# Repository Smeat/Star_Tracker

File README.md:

# Goals of this fork
 * Add support for esp32
 * Use an sdmmc driver and be able to use a larger library
   * SIMBAD library for Vmag <11 is about 16mb for the data and 30mb for the names
 * Use a nokia 5110 LCD with red backlight LEDs
 * Visual representation on the screen
 * WiFi connection to KStars/Stellarium -> done with LX200
 * ESP32 support only for now (8bit support may return once the esp32 is running)
# Arduino Star Tracker

This project aims an **automatic control for telescopes**, is **based on Arduino** and is **low-cost**!

The control utilizes a calibration method and various settings which enable you to control **any type of mount** (not just equatorial and altazimuthal) pointed at any direction.

The **total cost** of upgrading your mount should be around **75 USD** (*SkyWatcher SynScan GOTO Upgrade for EQ3-2* costs around *460 USD*).

## Features

See [future work](#future-work) for missing features (like communication via USB or Bluetooth). Some implemented and working freatures:

* **Manual control** with various precision (degrees, arc minutes and arc seconds).
* **Automatic pointing** at predefined coordinates.
* Onboard **catalogue of deep sky objects** (the one which is present in Stellarium), so you can search thousands of Messier, Caldwell and NGC objects.
* Precise **tracking** (for any type of mount).
* **Parking** to default position.
* **Calibration** of **mount pole** which works similarly to All-Star polar alignement.
* **Camera control** which alows you to take photos with predefined exposure time and with a predefined period.
* **Wireless control** via IR remote control.
* Real **asynchronous** control of **stepper motors** (any other code can be run in parallel). 
* **LX200** support

## Hardware setup

#### 0. What you will need:
* **Arduino MEGA2560**, unfortunately Arduino Uno cannot be used due to the lack of memory
* **Power supply** or battery, e.g. *12V* and around *2.5A* (depends on your stepper motors)
* *2×* **NEMA 17** stepper motor (forget about 28BYJ!)
* *2×* stepper motor driver like **A4988**
* *2×* stepper driver **extender for A4988** (we will modify this part, so you should consider custom design with 100μF capacitor)
* *4×* **4k7** or **10k resistor** (or any other suitable resistor you hold in your hands)
* *(optionally)* **Gearboxes** for the motors (battery screwdriver is typically much cheaper than profi gearboxes and has some planetary gearboxes inside!)
* *2×* **flexible shaft couplers** for joing the motors with mount
* **Real Time Clock**, note that *DS3231* or more precise clocks are preffered over DS1307 
* **microSD Card module**
* **16×2 LCD** (without I2C module)
* **10k Potentiometer**
* **IR receiver**
* **Remote control**, you can use your favourite one you use for TV or you can use any other for makers! This repo settings match with a [remote control](https://www.makeblock.com/project/me-ir-remote-controller) by Makeblock. 
* Some kind of **transistor**, e. g. *BC337* and suitable resistor, e. g. *1k ohms* 
* **Bunch of wires and connectors**

#### 1. Parts modification and tuning

You should **add** the four **resistors** between `STEP`-`GND` and `DIR`-`GND` pins **to avoid a jitter** of stepper motors at startup. 

A typical extender for A4988 has an `ENABLE` pin, however, we do not need it. Instead, we **need a pin for controlling microstepping**. That is why you should hardwire the three microstepping pins and you should add a single pin to control them. Search for *microstepping resolution truth table* of A4988.

A **cheap IR remote control** might have a **weak diode**. In that case, you won't be able to control the mount from a distant places. So I recommend you to **replace the diode with a better one.**  

You also need to **tune potentiometers of stepper drivers**. Search for *How to set output current limit on A4988 stepper driver*. This can reduce noise produced by the motors or you can remove **problems with skipping of steps**. 

Use the **potentiometer** connected to the LCD to **adjust contrast**.

#### 2. Wiring

## Software Settings & Uploding to Arduino

#### 0. Prepearing libraries

The following list contains libraries you will need to sucessfuly compile the Star Tracker project (most of them is included in the Arduino IDE by default):

* [RTCLib](https://github.com/adafruit/RTClib)
* [LiquidCrystal](https://github.com/arduino-libraries/LiquidCrystal)
* [SD](https://github.com/arduino-libraries/SD)
* [SPI](https://www.arduino.cc/en/Reference/SPI)
* [Wire](https://www.arduino.cc/en/Reference/Wire)
* [EEPROM](https://www.arduino.cc/en/Reference/EEPROM)

At first, **make sure you have already installed all the libraries**.

#### 1. General configuration

Next, you should **modify** the `src/config.h` file to fit your needs. Familiarize yourself with all the definitions in the file. You should **definitely change** `LONGITUDE`, `LATITUDE`, `REDUCTION_RATIO_xx` and `DEG_PER_MOUNT_REV_xx` variables! You also need to change `DEFAULT_POLE_xx` if you use an altazimuthal mount.

You may encounter a problem with **stucked motors**. In that case, I advice you to **adjust** `ACCEL_STEPS_xx`, `ACCEL_DELAY_xx`, `FAST_DELAY_START_xx` and `FAST_DELAY_END_xx`. Change these definitions in order to change motors speed or ac/deceleration.

#### 2. Remote control

You need to **change definitions of key codes** to fit the protocol used by your favourite remote control. Take look **at the beginning** of the `src/keypad.h` file. There are few definitions of `KP_KEY_xx` where `xx` describes the particular key. To figure out **codes used by your remote control**, upload the following sketch to your Arduino:

```
#include <Arduino.h>
#include <IRremote.h>
#include "src/config.h"

IRrecv ir(KEYPAD_IR_PIN);
decode_results results;

void setup(){
    Serial.begin(9600);
    ir.enableIRIn();
}

void loop(){
    if (!ir.decode(&results)) {
      delay(5);
      return;
    }
    Serial.println(results.value, HEX);
    ir.resume();
    delay(500);
}
```

Then **open the Serial monitor** and **observe the key codes** of pressed keys. Note that you will receive `0xFFFFFFFF` when you hold a key continuously.

You can also **change mapping of these keys to particular actions** in the `src/control.h` file (but be careful as these keys and actions should not cause conflicts and ambiguity).

#### 3. SD card and catalogue

Take an **empty and formatted microSD** card and **copy there the content** of the `SD` directory. It should be a single file `catalog.csv` which is a limited version of **Stellarium catalogue of deep space objects**. You can delete or add object to this file, however the structure and meaning of columns should be preserved.

#### 4. Real Time Clock

The `src/rtc_ds3231.h` file contains implementation of `Clock` class for `DS3231` module. In case you use **other module** or you want to obtain time from NTP servers, **implement** the `Clock` interface and change some lines in `Star_Tracker.ino`.

#### 5. Camera trigger

Similarly, you may need to change the implementation of the camera trigger control. The `src/CanonEOS1000D.h` file contains implementation of `CameraController` class for *Canon EOS1000D*. If you have other camera with **other trigger logic**, you should **create a new implementation** of `CameraController` and change some lines at `Star_Tracker.ino`. Note that in this case, you may also need a different wiring!

## Notes on precision

The only loss of precision is caused by Arduino's floating point unit which cannot work with 64-bit floating point numbers. Especially while computing extremal values of some goniometric funcions (tangens and other functions which are reduced to computing tangens). These problems can occur while pointing to stars near celestial pole. The GoTo feature can miss few arc minutes and alignement can be imprecise in that case. However points with lower DEC values should be handled properly.  

The tracking with very badly aligned mount can also be imprecise after some time because the speeds of DEC and RA motors are computed just once at the start of the movement. Unfortunately these speeds does not have to be constant necessarily.

## Future work

- [ ] enable **serial communication** with *USB* and *Bluetooth*
- [ ]  better **speed** computation **while tracking**
- [ ]  compute **alignment analytically**

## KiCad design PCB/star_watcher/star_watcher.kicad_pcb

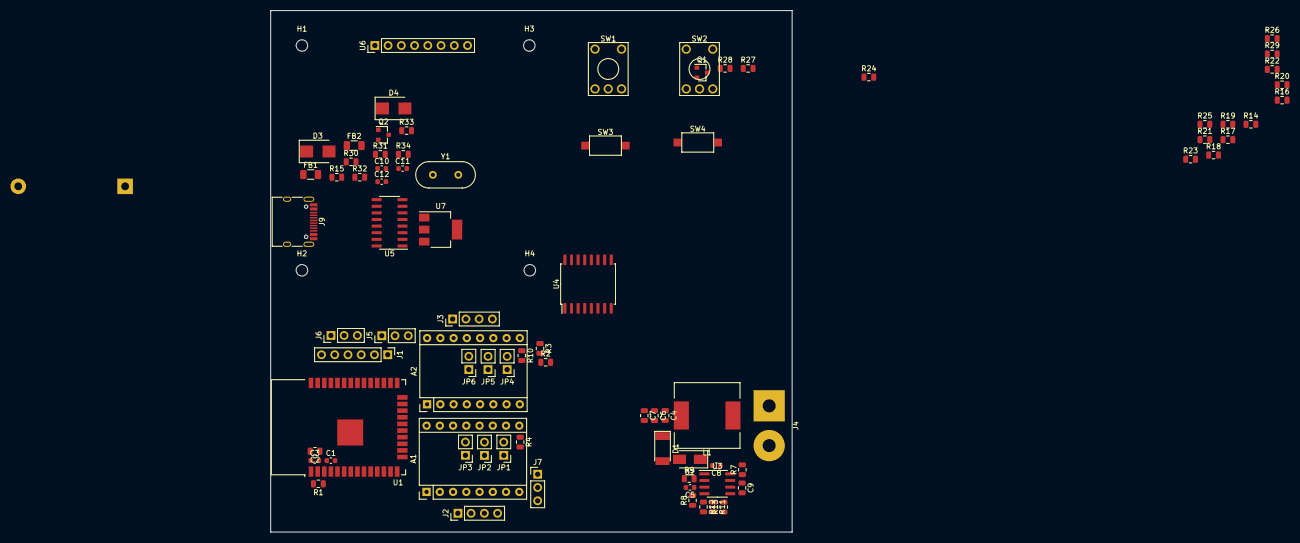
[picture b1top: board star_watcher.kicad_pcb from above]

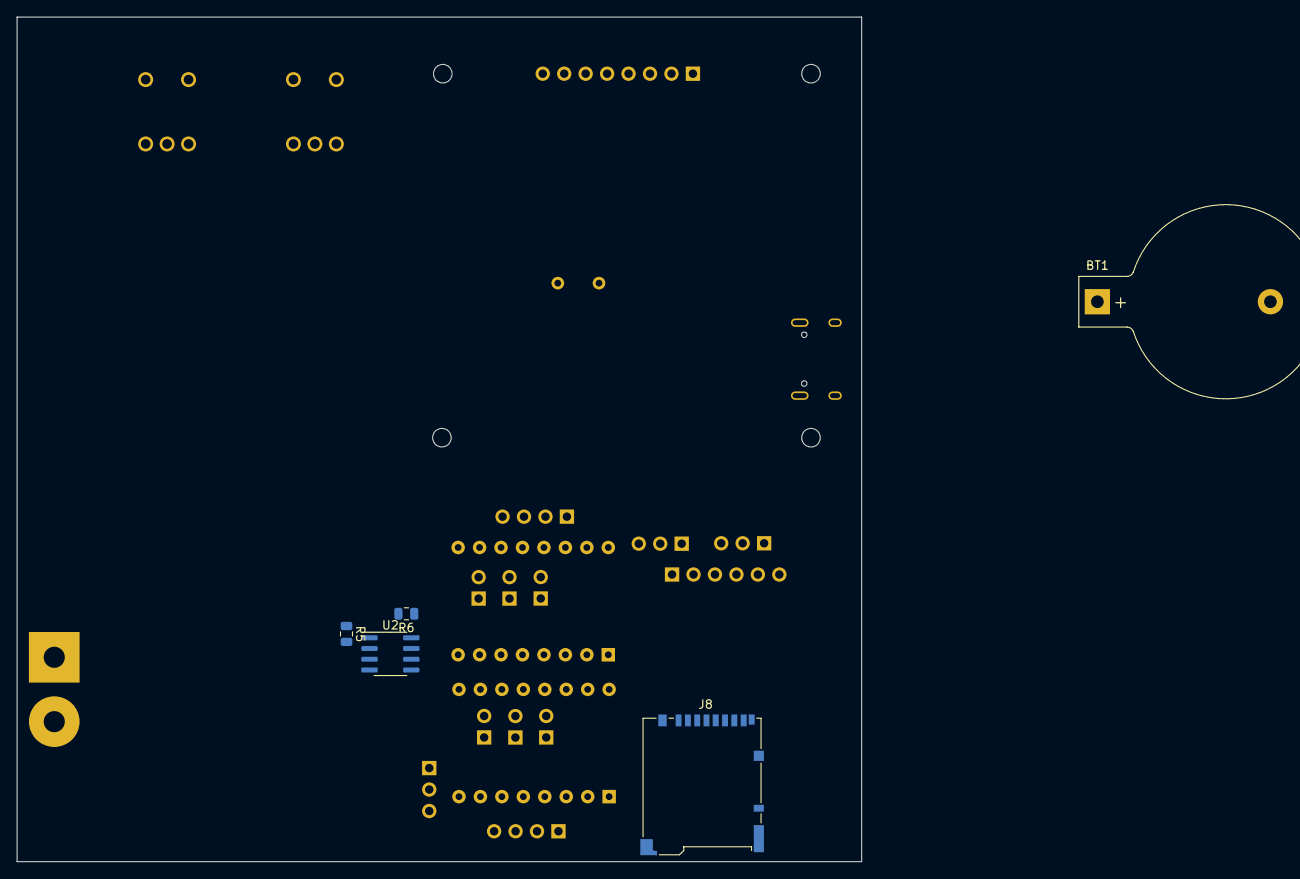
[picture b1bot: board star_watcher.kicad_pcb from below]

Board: 2 copper layers, 100.0 x 100.0 mm, 89 parts (5 on the bottom side), 78 nets, no tracks yet.

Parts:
A1, A2: Pololu_Breakout_A4988; Pololu_Breakout-16_15.2x20.3mm
BT1: Battery_Cell; BatteryHolder_Keystone_103_1x20mm
C1, C3, C8, C10: 0.1µF; C_0603_1608Metric
C2, C4, C6, C7, C9: 10µF; C_0805_2012Metric
C5: 150pF; C_0603_1608Metric
C11, C12: C; C_0603_1608Metric
D1: 3.5; D_MELF
D2: D_Schottky; D_SMA
D3, D4: D_TVS; D_SMB
FB1, FB2: Ferrite_Bead; L_1206_3216Metric
H1, H2, H3, H4: MountingHole; MountingHole_2.2mm_M2
J1: Programming; PinHeader_1x06_P2.54mm_Vertical
J2: Motor2; PinHeader_1x04_P2.54mm_Vertical
J3: Motor1; PinHeader_1x04_P2.54mm_Vertical
J4: input power; SolderWirePad_1x02_P7.62mm_Drill2.5mm
J5: UART1; PinHeader_1x03_P2.54mm_Vertical
J6: UART2; PinHeader_1x03_P2.54mm_Vertical
J7: I2C; PinHeader_1x03_P2.54mm_Vertical
J8: Micro_SD_Card_Det; microSD_HC_Hirose_DM3BT-DSF-PEJS
J9: USB_C_Receptacle_USB2.0; USB_C_Receptacle_HRO_TYPE-C-31-M-12
JP1, JP2, JP3, JP4, JP5, JP6: Jumper; PinHeader_1x02_P2.54mm_Vertical
L1: 22µH; L_12x12mm_H6mm
Q1, Q2: Q_PMOS_DGS; SOT-23
R1, R3, R4, R5, R6, R17, R18, R19, R20, R21, R22, R23, R24, R25, R26, R27, R28, R29: 10k; R_0805_2012Metric
R2: 240k; R_0805_2012Metric
R7, R8, R10: 100k; R_0805_2012Metric
R9: 59k; R_0805_2012Metric
R11, R14, R15, R16, R30, R31, R32, R33, R34: R; R_0805_2012Metric
R12: 40.2k; R_0805_2012Metric
R13: 200k; R_0805_2012Metric
SW1, SW2: Rotary_Encoder_Switch; KSA_Tactile_SPST
SW3, SW4: SW_Push; SW_SPST_CK_RS282G05A3
U1: ESP32-WROOM-32U; ESP32-WROOM-32
U2: DS3231MZ; SOIC-8_3.9x4.9mm_P1.27mm
U3: MP1584; SOIC-8_3.9x4.9mm_P1.27mm
U4: PCF8574; SOIC-16W_7.5x10.3mm_P1.27mm
U5: CH340G; SOIC-16_3.9x9.9mm_P1.27mm
U6: 5110; PinHeader_1x08_P2.54mm_Vertical
U7: AMS1117; SOT-223
Y1: 12MHz; Crystal_HC49-4H_Vertical

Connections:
+3V3: A1.2, A2.2, C2.1, C3.2, C4.2, C6.2, C7.2, D1.1, J1.2, J8.4, JP1.1, JP2.1, JP3.1, JP4.1, JP5.1, JP6.1, L1.2, Q1.3, Q2.3, R1.2, R4.2, R5.1, R6.1, R10.2, R11.2, R14.1, R17.1, R18.1, R19.1, R20.1, R21.1, R22.1, R23.2, R24.2, R25.1, R26.1, R27.1, R28.1, R29.1, U1.2, U2.2, U4.16, U5.4, U5.16, U6.6
+28V: A1.8, A2.8, C9.1, J4.1, Q2.2, R2.2, R7.1, R34.1, U3.7
/3.3V_USB: Q2.1, R32.1, U7.2, U7.4
/CE_5110: U1.27, U6.2
/DC_5110: U1.29, U6.3
/DIR1: A2.16, U1.28
/DIR2: A1.16, U1.31
/DTR: J1.3, SW4.1, U1.25, U5.13
/EN1: A2.9, R10.1
/EN2: A1.9, R4.1
/LCD_BACKLIGHT: Q1.2, U1.11
/PUSH1: R14.2, SW3.1, U1.5
/ROTARY1_A: R24.1, SW1.5, U4.7
/ROTARY1_B: R26.2, SW1.3, U4.9
/ROTARY1_PUSH: R27.2, SW1.1, U4.5
/ROTARY2_A: R23.1, SW2.5, U4.6
/ROTARY2_B: R25.2, SW2.3, U4.10
/ROTARY2_PUSH: R28.2, SW2.1, U4.4
/RST_5110: R29.2, U4.11, U6.1
/RTC_RST: U2.4, U4.12
/RTS: C1.1, J1.4, R1.1, U1.3, U5.14
/RX0: J1.5, U1.34, U5.2
/RX1: J5.2, U1.7
/RX2: J6.2, U1.6
/SCL: J7.2, R6.2, U1.37, U2.8, U4.14
/SDA: J7.1, R5.2, U1.36, U2.7, U4.15
/SD_CLK: J8.5, R21.2, U1.13
/SD_CMD: J8.3, R22.2, U1.23
/SD_D0: J8.7, R17.2, U1.24
/SD_D1: J8.8, R18.2, U1.26
/SD_D2: J8.1, R20.2, U1.14
/SD_D3: J8.2, R19.2, U1.16
/SPI_MOSI: U1.9, U6.4
/SPI_SCK: U1.8, U6.5
/STEP1: A2.15, U1.30
/STEP2: A1.15, U1.33
/TX0: J1.6, U1.35, U5.3
/TX1: J5.1, U1.10
/TX2: J6.1, U1.12
/USB_D+: D3.1, J9.A6, J9.B6, U5.5
/USB_D-: D4.2, J9.A7, J9.B7, U5.6
/VBUS: FB2.1, U7.3
/V_BAT_SENSE: R2.1, R3.2, U1.4
GND: A1.1, A1.7, A2.1, A2.7, BT1.2, C1.2, C2.2, C3.1, C4.1, C6.1, C7.1, C9.2, C10.1, C11.2, C12.2, D1.2, D2.2, D3.2, D4.1, FB1.2, J1.1, J4.2, J5.3, J6.3, J7.3, J8.6, J8.11, R3.1, R8.1, R9.1, R12.2, R13.1, R15.2, R30.1, R31.1, R33.2, R34.2, SW1.2, SW1.4, SW2.2, SW2.4, SW3.2, SW4.2, U1.1, U1.15, U1.38, U1.39, U2.5, U3.5, U4.1, U4.2, U4.3, U4.8, U5.1, U6.8
unnamed: A1.3, J2.1
unnamed: A1.4, J2.2
unnamed: A1.5, J2.3
unnamed: A1.6, J2.4
unnamed: A1.10, JP1.2
unnamed: A1.11, JP2.2
unnamed: A1.12, JP3.2
unnamed: A1.13, A1.14
unnamed: A2.3, J3.1
unnamed: A2.4, J3.2
unnamed: A2.5, J3.3
unnamed: A2.6, J3.4
unnamed: A2.10, JP4.2
unnamed: A2.11, JP5.2
unnamed: A2.12, JP6.2
unnamed: A2.13, A2.14
unnamed: BT1.1, U2.6
unnamed: C5.1, U3.3
unnamed: C5.2, R8.2
unnamed: C8.1, U3.8
unnamed: C8.2, D2.1, L1.1, U3.1
unnamed: C10.2, J9.S1, R15.1
unnamed: C11.1, U5.7, Y1.1
unnamed: C12.1, U5.8, Y1.2
unnamed: FB1.1, J9.A1, J9.A12, J9.B1, J9.B12
unnamed: FB2.2, J9.A4, J9.A9, J9.B4, J9.B9
unnamed: J9.A5, R30.2
unnamed: J9.B5, R31.2
unnamed: Q1.1, R16.2
unnamed: R7.2, R9.2, U3.2
unnamed: R11.1, R12.1, U3.4
unnamed: R13.2, U3.6
unnamed: R16.1, U6.7
unnamed: R32.2, R33.1, U7.1

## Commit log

2020-04-06 Move to platformio
2020-04-06 Fix wrong comparison
2020-04-06 Fix a bunch of warnings
2020-04-06 [WIP] Make it _compilable_ on esp32. _NOT FUNCTIONAL_
2020-04-06 Update gitignore.
2020-04-07 Change all floats to double. If avr-gcc is compiled with -mfloat=64 you can get 64bit floating point on the atmega as well. If not they are just normal floats
2020-04-07 Rename DEBUG defines to avoid collisions
2020-04-07 Fix esp32 compilation with debug enabled
2020-04-09 Fix display pins
2020-04-09 Add tcp socket
2020-04-09 Use the GPLv3 for now Might change that later again
2020-04-09 Remove all old float constants
2020-04-09 Add wifi support
2020-04-09 Add verbose log for debugging
2020-04-09 [WIP] LX200 protocol Still need to figure out how exactly the coordinate system works e.g. when to use global/local and everything
2020-04-09 Add script to generate image file
2020-04-09 [WIP] Add pcb
2020-04-09 Use pointers for output variables
2020-04-09 Add better names
2020-04-09 Use freertos queue
2020-04-09 Way too large commit. Not crashing on esp32 now Add a target command to use with lx200
2020-04-09 Add comment to readme about 8bit support
2020-04-10 Remove debug calls
2020-04-10 Add ACK response
2020-04-10 Add support for getting the current target
2020-04-10 KStars seems to have RA and DEC switched? I am probably just too dumb
2020-04-10 Fix format
2020-04-10 Add a bunch of LX200 commands and fix old ones
2020-04-10 Add 64µS interrupt for esp32
2020-04-10 Fix LX200 dec
2020-04-10 Change steps for easy debugging
2020-04-10 Add debug task
2020-04-10 Fix pin init on esp32
2020-04-10 Working debug version (simulated steps)
2020-04-10 Working without microstepping
2020-04-11 Working with smaller values Removes old atmega code Add pin toggle for debugging loop stability The direction is now a variable instead of using the pin as a variable
2020-04-11 Fix negative dec in LX200 message
2020-04-11 Add speed management back
2020-04-11 Use primitive tracking for now Just constantly updating the target. Still need to test if this works once I get the hardware
2020-04-11 Make longitude a runtime configuration
2020-04-11 Add a bunch of LX200 commands
2020-04-11 Change date format
2020-04-11 Mark LX200 as implemented
2020-04-11 Double is working as well
